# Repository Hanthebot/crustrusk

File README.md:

# Crustrusk

Modular, adjustable column-staggered (split) keyboard project

## Features
- adjustable stagger / modular PCBs
- implement up to 5x7+7 column stagger keyboard
- support I2C / SPI communication for peripherals

## What it can do
- default bundle can give you 3x7+3 keyboard with knob
  - e.g. corne with extra key in inner column & knob
- adjusting stagger to fit your hand
  - you can make it ortho too
- adjusting splay to fit your hand
- (technically) support display, trackball, touchpad, etc.
- implement:
  - Corne
  - Cheapino
  - Sweep
  - Sofle
  - Cornix
  - Flake
  - Totem (with custom column PCB)
  - Jian (with custom column PCB)
  - Lily58 (with custom column PCB)
  - Kyria
  - Ergodox
  - Moonlander
  - Crosses (technically)
  - ...

## What it cannot do
- keywell structure, unless PCB is modified that key
- row-staggered
- semi-staggered

## Remarks
### Production
- current version of 'bundle' is not production tested
  - old gerber that is initially committed was tested, although JST sockets on the main board had to be flipped.
  - male to male connector tips to face the same side: [reminder](https://github.com/ReSummit/Seismos#important-notes-for-building-keyboard)
- all PCB here are MX, but transition should be feasible
- bundles will, ideally, be sub-102x102 mm for cheap fabrication
### Engineering decisions
- JST PH socket is chosen because:
  - cheap, flexible, easy to solder, not too big
  - it's not the most aesthetic / professional choice
  - smaller JST sockets are SMD and harder to solder with small pitch
    - they do offer smaller height and greater surface, though
  - FFC sockets are great, but the sided nature and flexibilities were my concern
- 6 pins for general case was used as:
  - some popular keyboards have 5-key column / thumb cluster, and I wanted to cover them
- 8 pins for extended thumb / peripheral was used as:
  - Ergodox / Kyria uses 6+ key thumb cluster
  - to support SPI / trackballs
  - high potential for peripheral development
- RP2040-zero was used as it's easy to solder without pins and exposes more pins
  - changing it to Pro-micro / xiao (with some sacrifices) shouldn't be too hard
  - core is ugly. Improvement is needed.
- currently, M2 screws & standoffs are used to fix the keyboard & adjust stagger.
### Building tips
- it'd be easier to use SMD diodes as THT diodes' leg might be touching the switches. I cut legs tightly and it was fine.
- web app for generating QMK config for various combinations are under way

## Inspirations
- [Zebra](https://github.com/nezumee/zebra)
- [Seismos](https://github.com/ReSummit/Seismos)
- [Pangaea](https://github.com/e3w2q/Pangaea-keyboard/tree/main)
- [Pineapple60-P4](https://github.com/saoto28/pineapple60/tree/main/p4)
- [Squalius-cephalus's modular keyboard](https://www.reddit.com/r/ErgoMechKeyboards/comments/1l3c5us/diy_modular_split_keyboard/)

## Disclaimer
- Any layout / designs used in this project that originates from other repositories (e.g. thumb clusters) follows the original author's license.

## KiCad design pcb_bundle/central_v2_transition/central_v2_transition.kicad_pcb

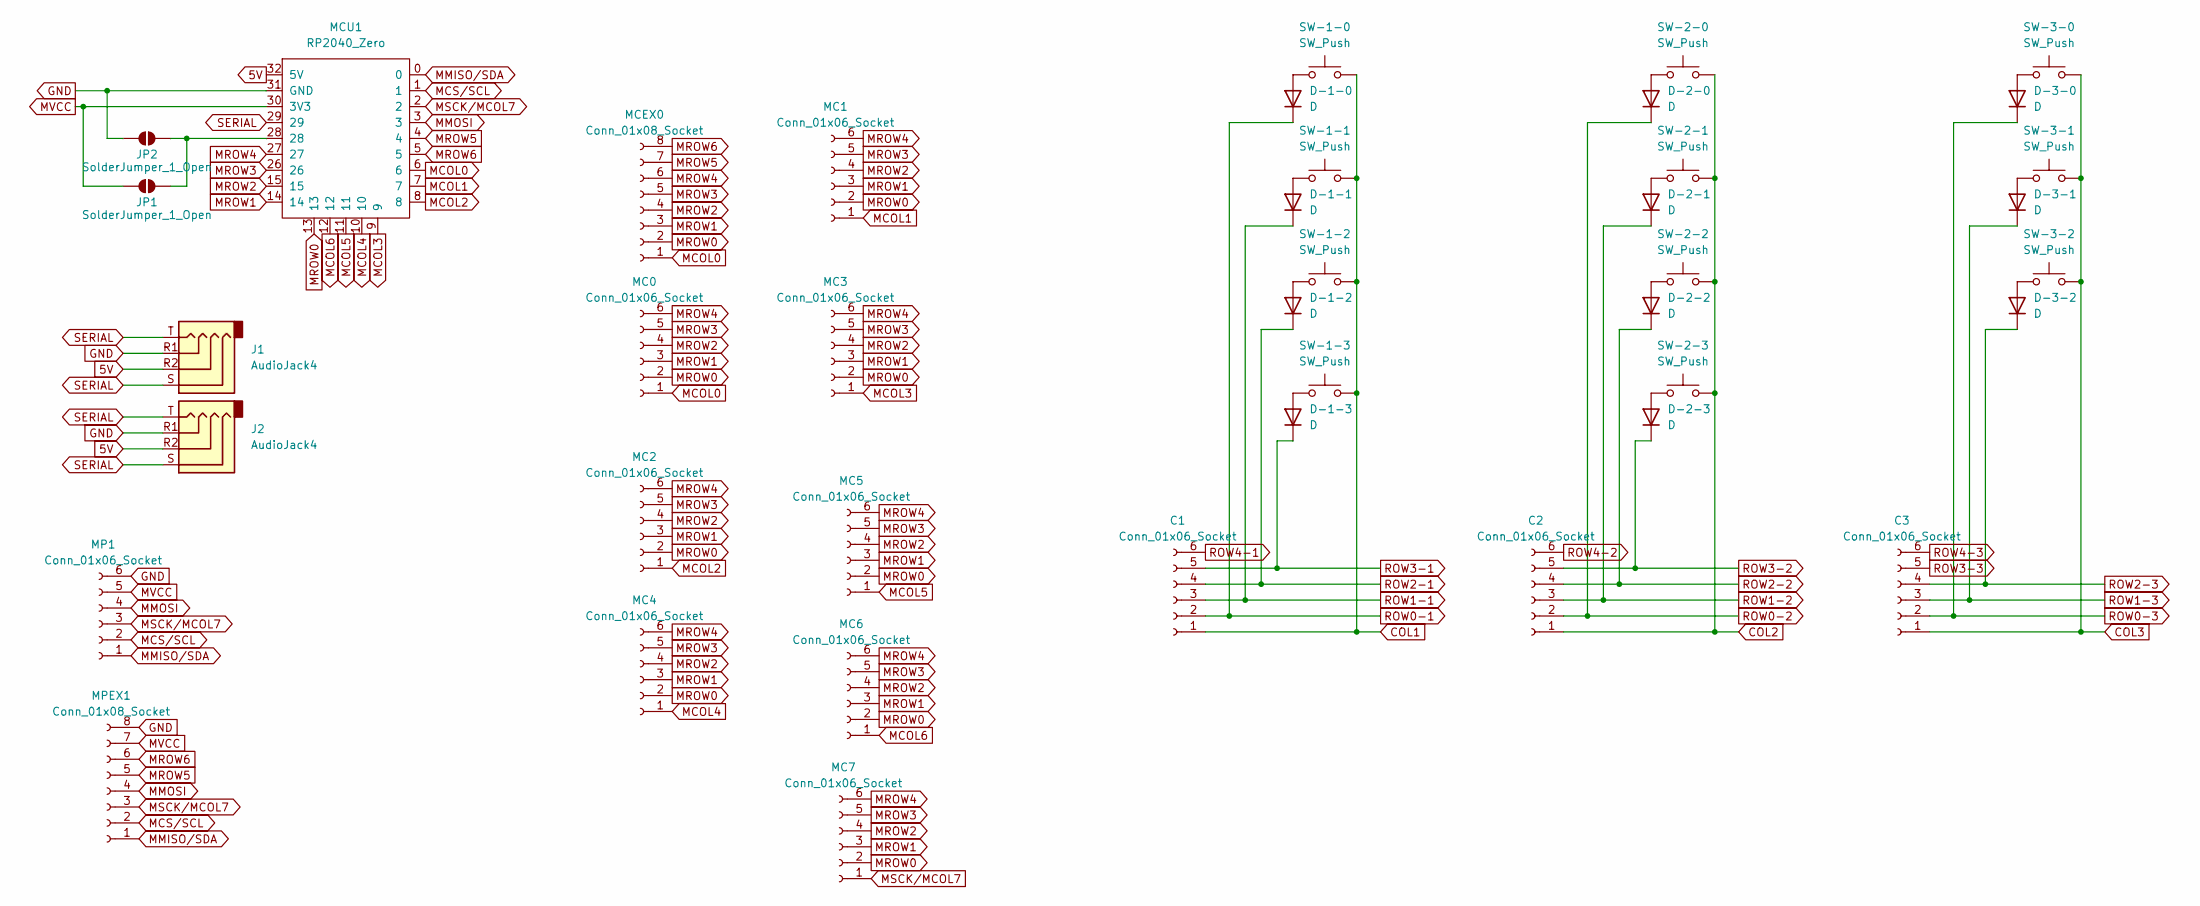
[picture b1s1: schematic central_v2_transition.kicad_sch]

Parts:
C1, C2, C3: Conn_01x06_Socket; reversible JST_PH_S6B-PH-K_1x06_P2.00mm_Horizontal
D-1-0, D-1-1, D-1-2, D-1-3, D-2-0, D-2-1, D-2-2, D-2-3, D-3-0, D-3-1, D-3-2: D; Diode_TH_SMD_REVERSIBLE
J1, J2: AudioJack4; TRRS-PJ-320A_PIN
JP1, JP2: SolderJumper_1_Open; SolderJumper-2_P1.3mm_Open_TrianglePad1.0x1.5mm
MC0, MC1, MC2, MC3, MC4, MC5, MC6, MC7: Conn_01x06_Socket; rev_JST_PH_B6B-PH-K_1x06_P2.00mm_Vertical
MCEX0: Conn_01x08_Socket; rev_JST_PH_B8B-PH-K_1x08_P2.00mm_Vertical
MCU1: RP2040_Zero; RP2040-Zero-THT-mm
MP1: Conn_01x06_Socket; rev_JST_PH_B6B-PH-K_1x06_P2.00mm_Vertical
MPEX1: Conn_01x08_Socket; rev_JST_PH_B8B-PH-K_1x08_P2.00mm_Vertical
SW-1-0, SW-1-1, SW-1-2, SW-1-3, SW-2-0, SW-2-1, SW-2-2, SW-2-3, SW-3-0, SW-3-1, SW-3-2: SW_Push; Kailh_hotswap_only_socket_MX_optional_reversible-MIRROR

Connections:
5V: J1.R2, J2.R2, MCU1.32 (5V)
COL1: C1.1, SW-1-0.2, SW-1-1.2, SW-1-2.2, SW-1-3.2
COL2: C2.1, SW-2-0.2, SW-2-1.2, SW-2-2.2, SW-2-3.2
COL3: C3.1, SW-3-0.2, SW-3-1.2, SW-3-2.2
GND: J1.R1, J2.R1, JP2.1 (A), MCU1.31 (GND), MP1.6, MPEX1.8
MCOL0: MC0.1, MCEX0.1, MCU1.6
MCOL1: MC1.1, MCU1.7
MCOL2: MC2.1, MCU1.8
MCOL3: MC3.1, MCU1.9
MCOL4: MC4.1, MCU1.10
MCOL5: MC5.1, MCU1.11
MCOL6: MC6.1, MCU1.12
MCS/SCL: MCU1.1, MP1.2, MPEX1.2
MMISO/SDA: MCU1.0, MP1.1, MPEX1.1
MMOSI: MCU1.3, MP1.4, MPEX1.4
MROW0: MC0.2, MC1.2, MC2.2, MC3.2, MC4.2, MC5.2, MC6.2, MC7.2, MCEX0.2, MCU1.13
MROW1: MC0.3, MC1.3, MC2.3, MC3.3, MC4.3, MC5.3, MC6.3, MC7.3, MCEX0.3, MCU1.14
MROW2: MC0.4, MC1.4, MC2.4, MC3.4, MC4.4, MC5.4, MC6.4, MC7.4, MCEX0.4, MCU1.15
MROW3: MC0.5, MC1.5, MC2.5, MC3.5, MC4.5, MC5.5, MC6.5, MC7.5, MCEX0.5, MCU1.26
MROW4: MC0.6, MC1.6, MC2.6, MC3.6, MC4.6, MC5.6, MC6.6, MC7.6, MCEX0.6, MCU1.27
MROW5: MCEX0.7, MCU1.4, MPEX1.5
MROW6: MCEX0.8, MCU1.5, MPEX1.6
MSCK/MCOL7: MC7.1, MCU1.2, MP1.3, MPEX1.3
MVCC: JP1.1 (A), MCU1.30 (3V3), MP1.5, MPEX1.7
unnamed: D-1-0.2 (A), SW-1-0.1
unnamed: D-1-1.2 (A), SW-1-1.1
unnamed: D-1-2.2 (A), SW-1-2.1
unnamed: D-1-3.2 (A), SW-1-3.1
unnamed: D-2-0.2 (A), SW-2-0.1
unnamed: D-2-1.2 (A), SW-2-1.1
unnamed: D-2-2.2 (A), SW-2-2.1
unnamed: D-2-3.2 (A), SW-2-3.1
unnamed: D-3-0.2 (A), SW-3-0.1
unnamed: D-3-1.2 (A), SW-3-1.1
unnamed: D-3-2.2 (A), SW-3-2.1
unnamed: JP1.2 (B), JP2.2 (B), MCU1.28
ROW0-1: C1.2, D-1-0.1 (K)
ROW0-2: C2.2, D-2-0.1 (K)
ROW0-3: C3.2, D-3-0.1 (K)
ROW1-1: C1.3, D-1-1.1 (K)
ROW1-2: C2.3, D-2-1.1 (K)
ROW1-3: C3.3, D-3-1.1 (K)
ROW2-1: C1.4, D-1-2.1 (K)
ROW2-2: C2.4, D-2-2.1 (K)
ROW2-3: C3.4, D-3-2.1 (K)
ROW3-1: C1.5, D-1-3.1 (K)
ROW3-2: C2.5, D-2-3.1 (K)
ROW3-3: C3.5
ROW4-1: C1.6
ROW4-2: C2.6
ROW4-3: C3.6
SERIAL: J1.S, J1.T, J2.S, J2.T, MCU1.29

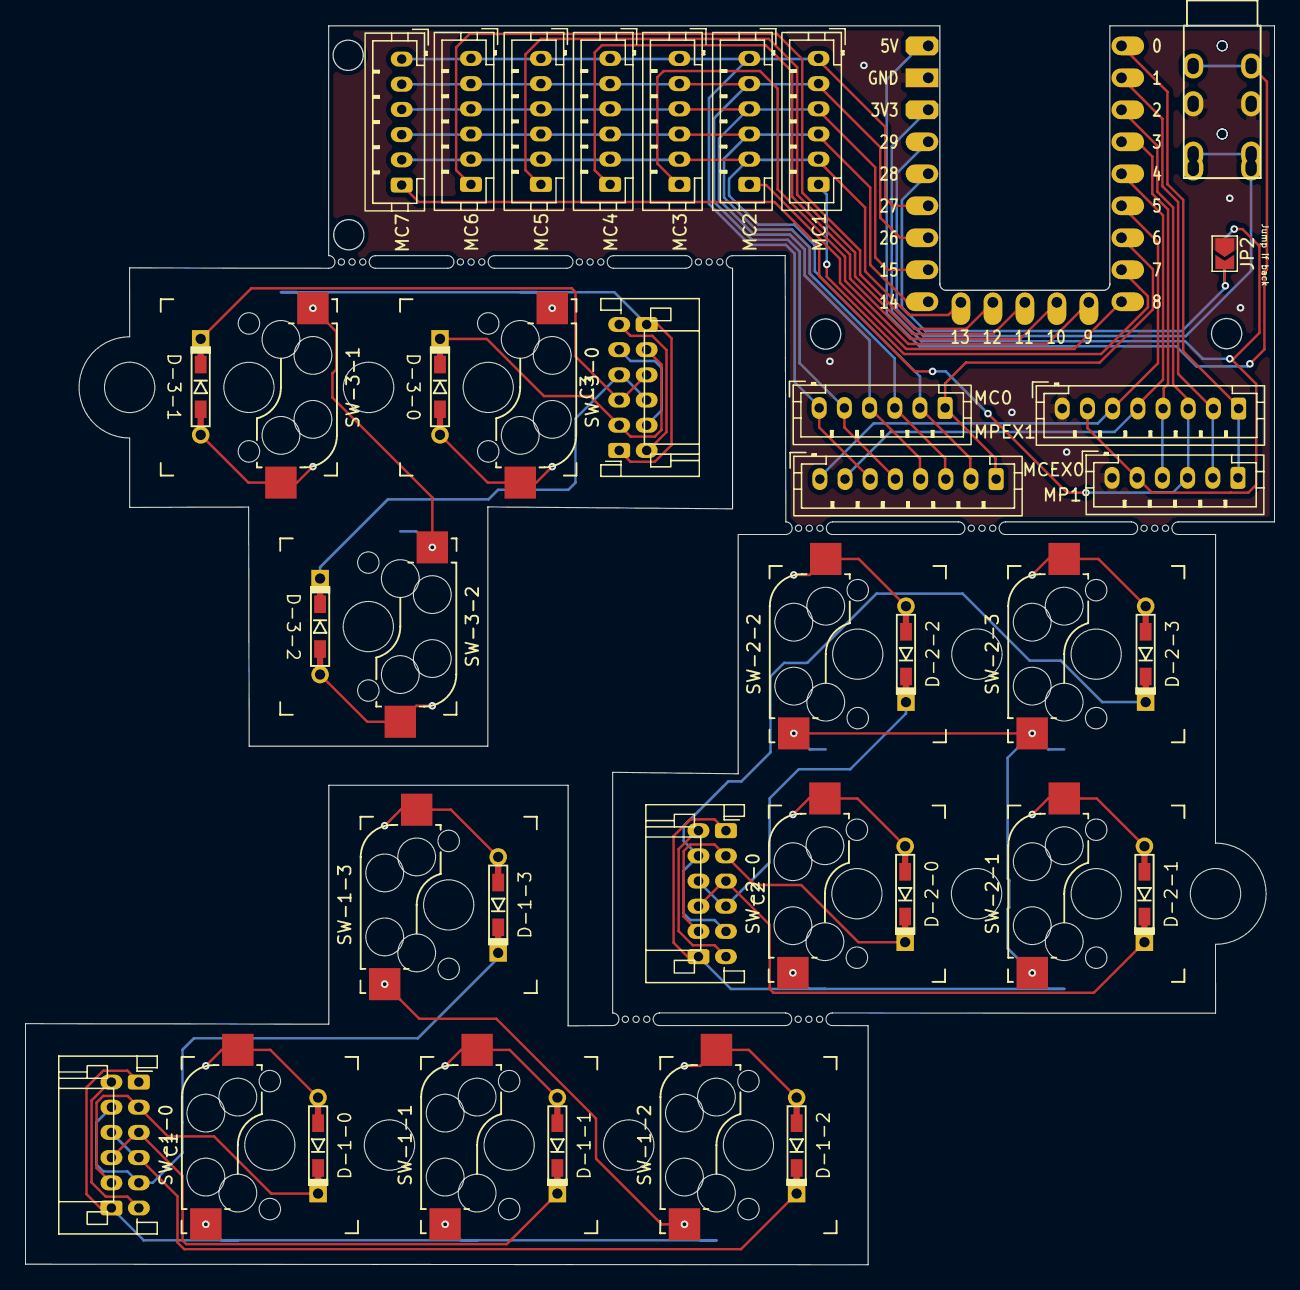
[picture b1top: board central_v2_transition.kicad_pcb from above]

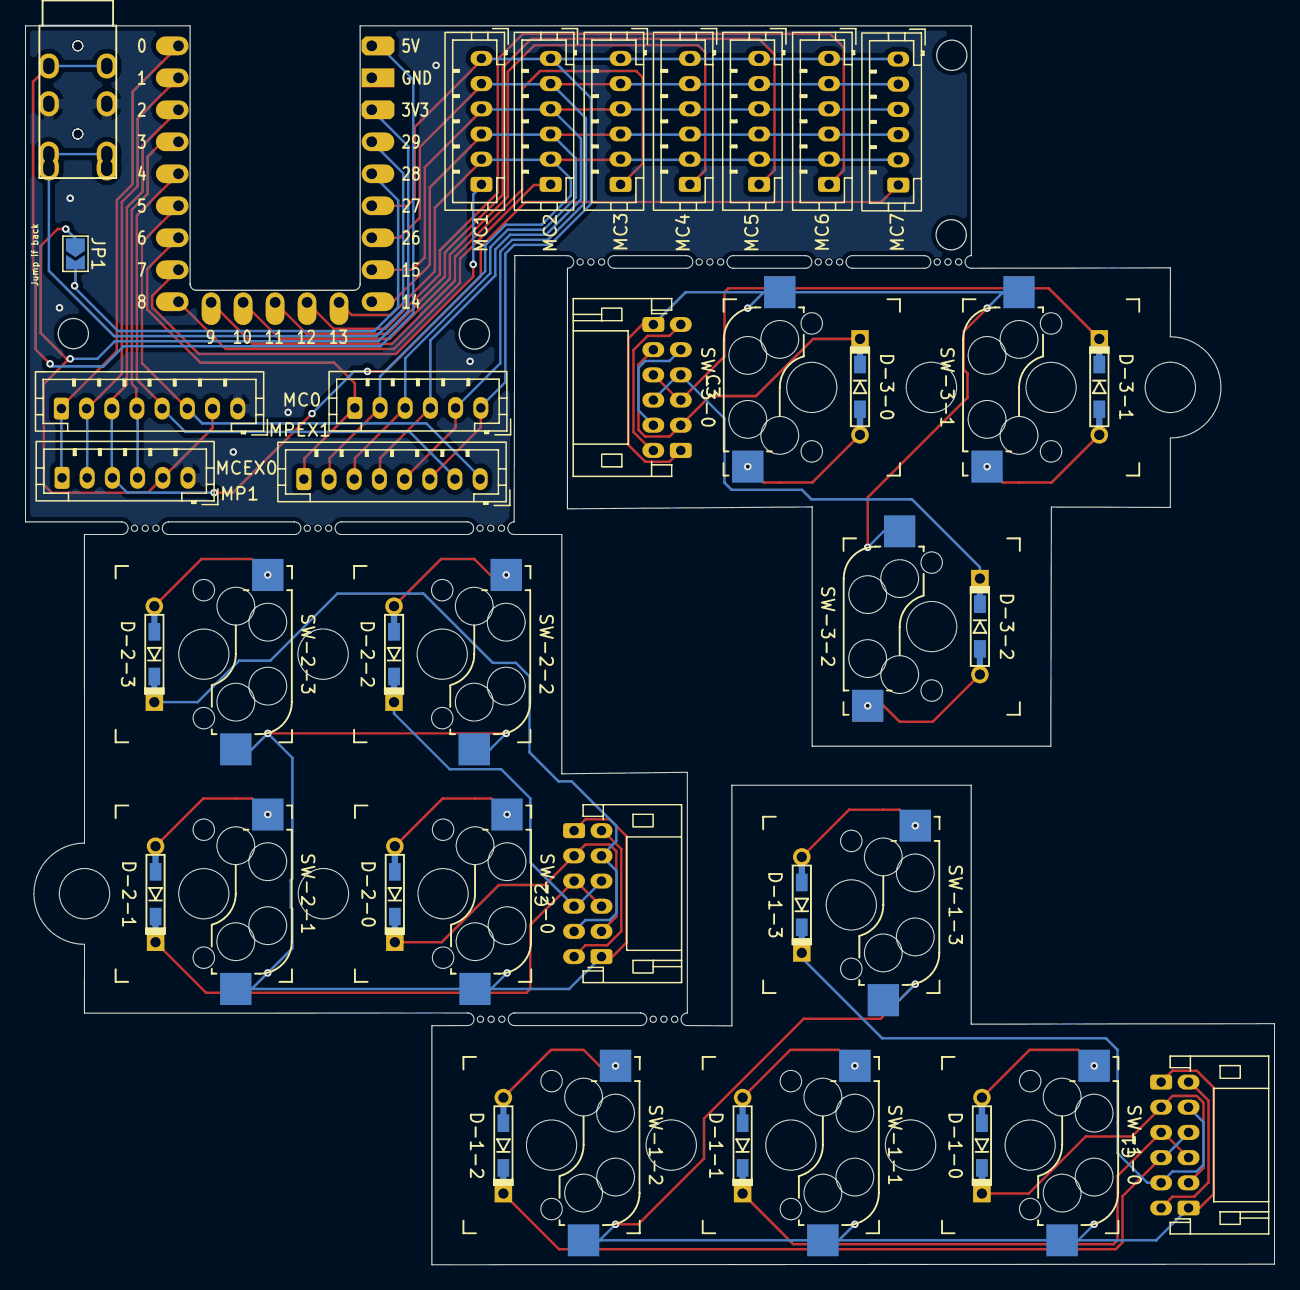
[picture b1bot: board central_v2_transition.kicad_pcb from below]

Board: 2 copper layers, 99.2 x 98.4 mm, 54 parts (2 on the bottom side), 48 nets.

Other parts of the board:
Ref**: Val**; hole-m2-screw
Ref**#2, Ref**#3, Ref**#4: Val**; hole-m2-screw
mouse-bite-1mm-3mm, mouse-bite-1mm-3mm#2, mouse-bite-1mm-3mm#3, mouse-bite-1mm-3mm#4, mouse-bite-1mm-3mm#5, mouse-bite-1mm-3mm#6, mouse-bite-1mm-3mm#7, mouse-bite-1mm-3mm#8, mouse-bite-1mm-3mm#9: VAL**; BreakLine_3h_D0.5mm_P0.85mm

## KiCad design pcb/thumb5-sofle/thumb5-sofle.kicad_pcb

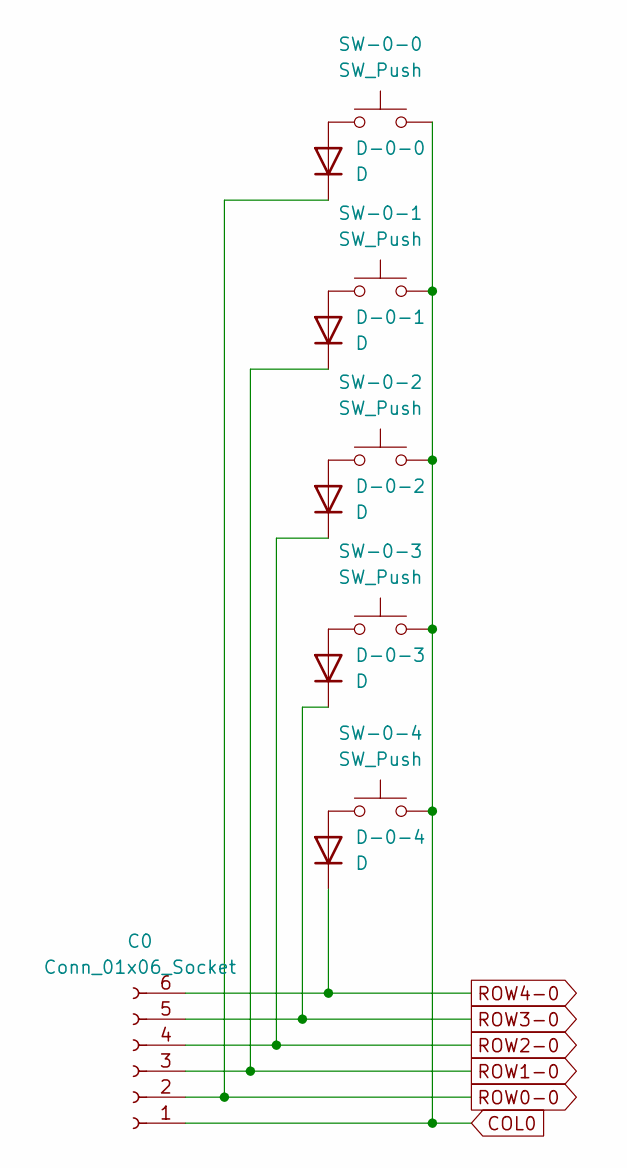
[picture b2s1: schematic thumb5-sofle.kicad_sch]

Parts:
C0: Conn_01x06_Socket; reversible JST_PH_S6B-PH-K_1x06_P2.00mm_Horizontal
D-0-0, D-0-1, D-0-2, D-0-3, D-0-4: D; Diode_TH_SMD_REVERSIBLE
SW-0-0, SW-0-1, SW-0-2, SW-0-3, SW-0-4: SW_Push; Kailh_hotswap_only_socket_MX_optional_reversible-MIRROR

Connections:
COL0: C0.1, SW-0-0.2, SW-0-1.2, SW-0-2.2, SW-0-3.2, SW-0-4.2
unnamed: D-0-0.2 (A), SW-0-0.1
unnamed: D-0-1.2 (A), SW-0-1.1
unnamed: D-0-2.2 (A), SW-0-2.1
unnamed: D-0-3.2 (A), SW-0-3.1
unnamed: D-0-4.2 (A), SW-0-4.1
ROW0-0: C0.2, D-0-0.1 (K)
ROW1-0: C0.3, D-0-1.1 (K)
ROW2-0: C0.4, D-0-2.1 (K)
ROW3-0: C0.5, D-0-3.1 (K)
ROW4-0: C0.6, D-0-4.1 (K)

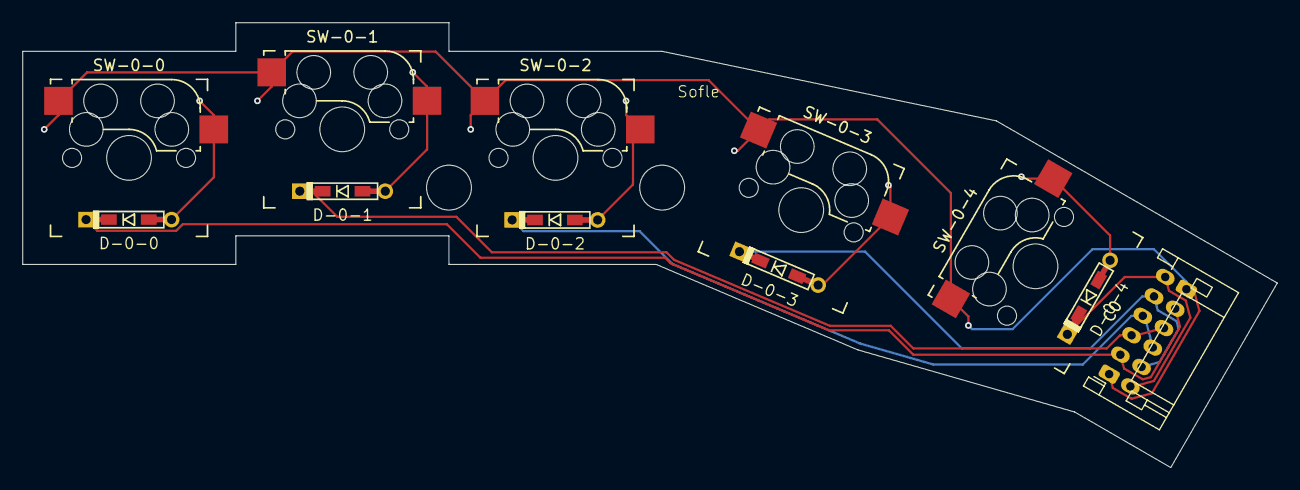
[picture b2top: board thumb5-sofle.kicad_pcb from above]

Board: 2 copper layers, 111.8 x 39.7 mm, 11 parts (0 on the bottom side), 11 nets.
